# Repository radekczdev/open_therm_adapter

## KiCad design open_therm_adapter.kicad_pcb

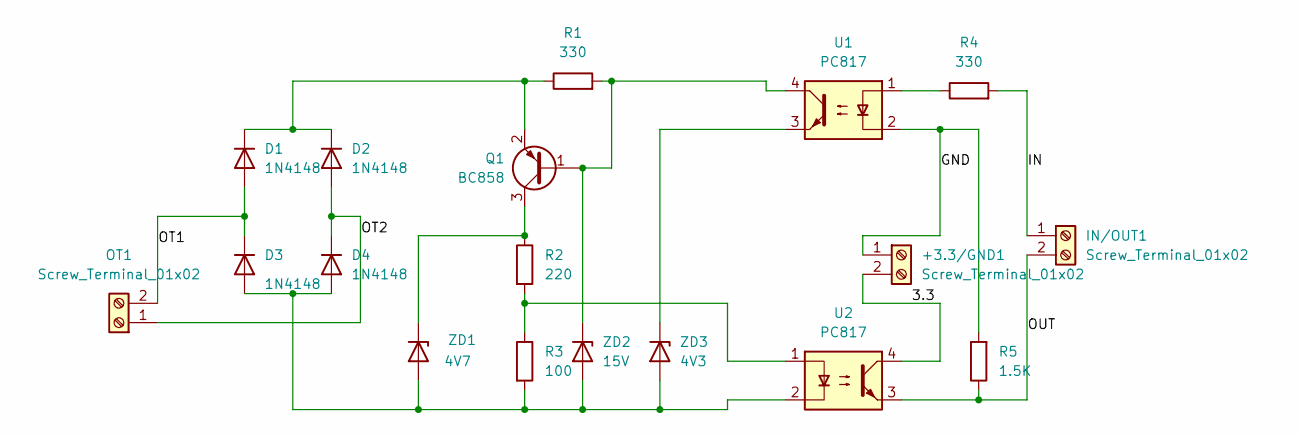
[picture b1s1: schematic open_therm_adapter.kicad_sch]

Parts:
+3.3/GND1: Screw_Terminal_01x02; TerminalBlock_bornier-2_P5.08mm
D1, D2, D3, D4: 1N4148; D_DO-35_SOD27_P7.62mm_Horizontal
IN/OUT1: Screw_Terminal_01x02; TerminalBlock_bornier-2_P5.08mm
OT1: Screw_Terminal_01x02; TerminalBlock_bornier-2_P5.08mm
Q1: BC858; SOT-23
R1, R4: 330; R_Axial_DIN0204_L3.6mm_D1.6mm_P5.08mm_Horizontal
R2: 220; R_Axial_DIN0204_L3.6mm_D1.6mm_P5.08mm_Horizontal
R3: 100; R_Axial_DIN0204_L3.6mm_D1.6mm_P5.08mm_Horizontal
R5: 1.5K; R_Axial_DIN0204_L3.6mm_D1.6mm_P5.08mm_Horizontal
U1, U2: PC817; DIP-4_W7.62mm
ZD1: 4V7; D_DO-35_SOD27_P7.62mm_Horizontal
ZD2: 15V; D_DO-35_SOD27_P7.62mm_Horizontal
ZD3: 4V3; D_DO-35_SOD27_P7.62mm_Horizontal

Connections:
/3.3: +3.3/GND1.2, U2.4
/GND: +3.3/GND1.1, R5.2, U1.2
/IN: IN/OUT1.1, R4.2
/OT1: D1.2 (A), D3.1 (K), OT1.2
/OT2: D2.2 (A), D4.1 (K), OT1.1
/OUT: IN/OUT1.2, R5.1, U2.3
unnamed: D1.1 (K), D2.1 (K), Q1.2 (E), R1.1
unnamed: D3.2 (A), D4.2 (A), R3.2, U2.2, ZD1.2 (A), ZD2.2 (A), ZD3.2 (A)
unnamed: Q1.1 (B), R1.2, U1.4, ZD2.1 (K)
unnamed: Q1.3 (C), R2.1, ZD1.1 (K)
unnamed: R2.2, R3.1, U2.1
unnamed: R4.1, U1.1
unnamed: U1.3, ZD3.1 (K)

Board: 2 copper layers, 18 parts (1 on the bottom side), 13 nets, no tracks yet.

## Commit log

2025-04-09 Open therm adapter kicad files
2025-04-09 modified gitignore
